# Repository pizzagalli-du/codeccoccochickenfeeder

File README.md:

# codeccoccochickenfeeder
Ultra low power chicken feeder

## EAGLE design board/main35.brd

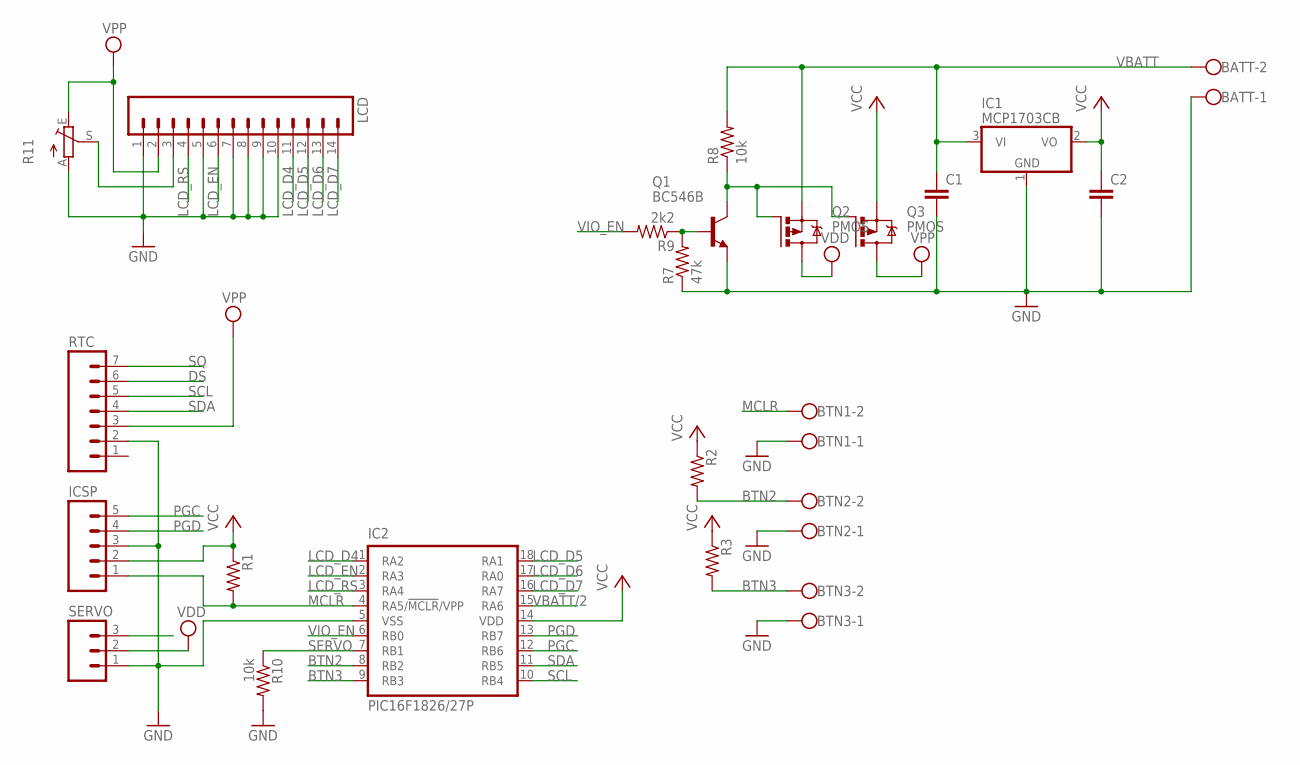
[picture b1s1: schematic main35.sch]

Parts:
BATT: W237-102
BTN1, BTN2, BTN3: W237-102
C1, C2: C-EUC0805K; C0805K
IC1: MCP1703CB; SOT23
IC2: PIC16F1826/27P; DIL18
ICSP: M05; 05P
LCD: M14; 14P
Q1: BC546B; TO92-EBC
Q2, Q3: PMOS; MICRO3
R1, R2, R3: R-US_M0805; M0805
R7: 47k; 0207/10
R8, R10: 10k; R1005
R9: 2k2; 0207/10
R11: TRIM_EU-LI10; LI10
RTC: M07; 07P
SERVO: M03; 03P

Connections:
BTN2: BTN2.2, IC2.8 (RB2), R2.2
BTN3: BTN3.2, IC2.9 (RB3), R3.2
DS: RTC.6
GND: BATT.1, BTN1.1, BTN2.1, BTN3.1, C1.2, C2.2, IC1.1 (GND), IC2.5 (VSS), ICSP.3, LCD.1, LCD.5, LCD.7, LCD.8, LCD.9, LCD.10, Q1.E, R7.1, R10.2, R11.A, RTC.2, SERVO.1
LCD_D4: IC2.1 (RA2), LCD.11
LCD_D5: IC2.18 (RA1), LCD.12
LCD_D6: IC2.17 (RA0), LCD.13
LCD_D7: IC2.16 (RA7), LCD.14
LCD_EN: IC2.2 (RA3), LCD.6
LCD_RS: IC2.3 (RA4), LCD.4
MCLR: BTN1.2, IC2.4 (RA5/!MCLR!/VPP), ICSP.1, R1.2
unnamed: LCD.3, R11.S
unnamed: Q1.B, R7.2, R9.1
PGC: IC2.12 (RB6), ICSP.5
PGD: IC2.13 (RB7), ICSP.4
SCL: IC2.10 (RB4), RTC.5
SDA: IC2.11 (RB5), RTC.4
SERVO: IC2.7 (RB1), R10.1, SERVO.3
SQ: RTC.7
VBATT: BATT.2, C1.1, IC1.3 (VI), Q2.2 (S), R8.2
VBATT/2: IC2.15 (RA6)
VCC: C2.1, IC1.2 (VO), IC2.14 (VDD), ICSP.2, Q3.2 (S), R1.1, R2.1, R3.1
VDD: Q2.3 (D), SERVO.2
VGIO: Q1.C, Q2.1 (G), Q3.1 (G), R8.1
VIO_EN: IC2.6 (RB0), R9.2
VPP: LCD.2, Q3.3 (D), R11.E, RTC.3

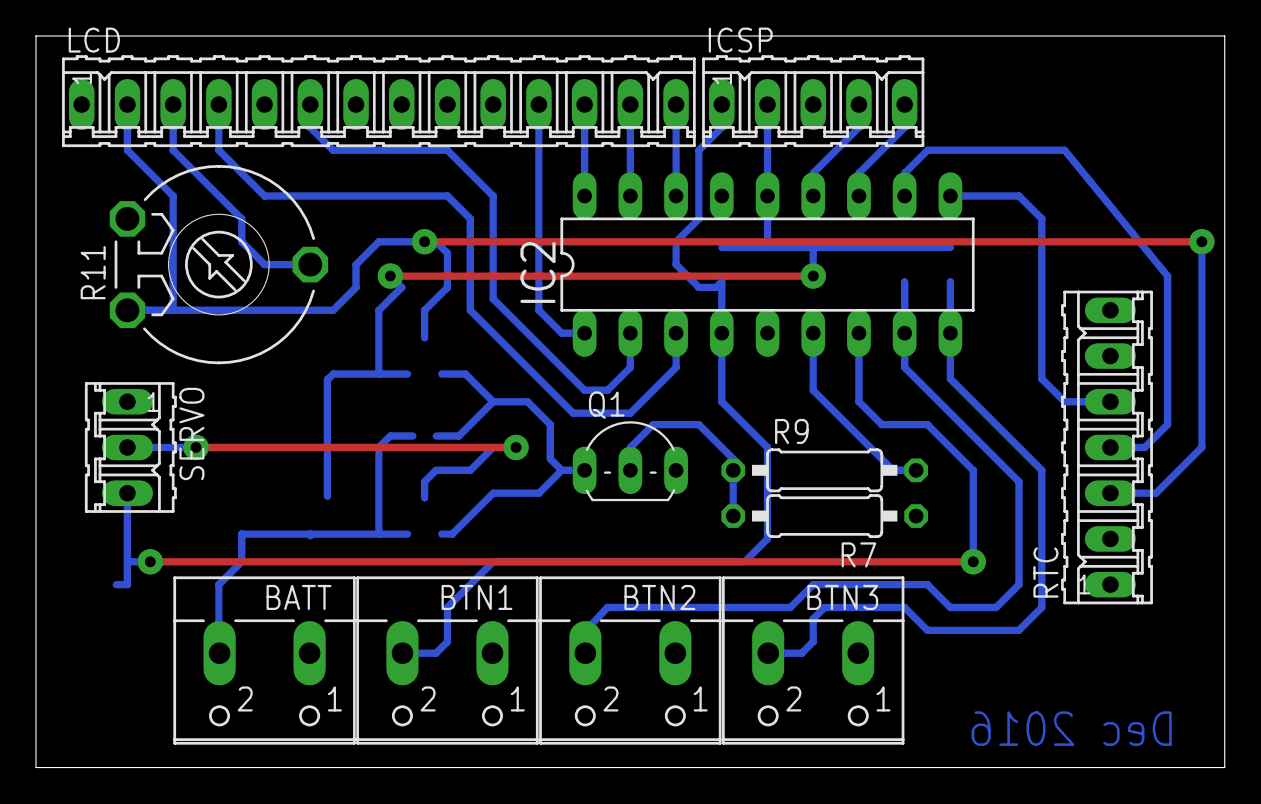
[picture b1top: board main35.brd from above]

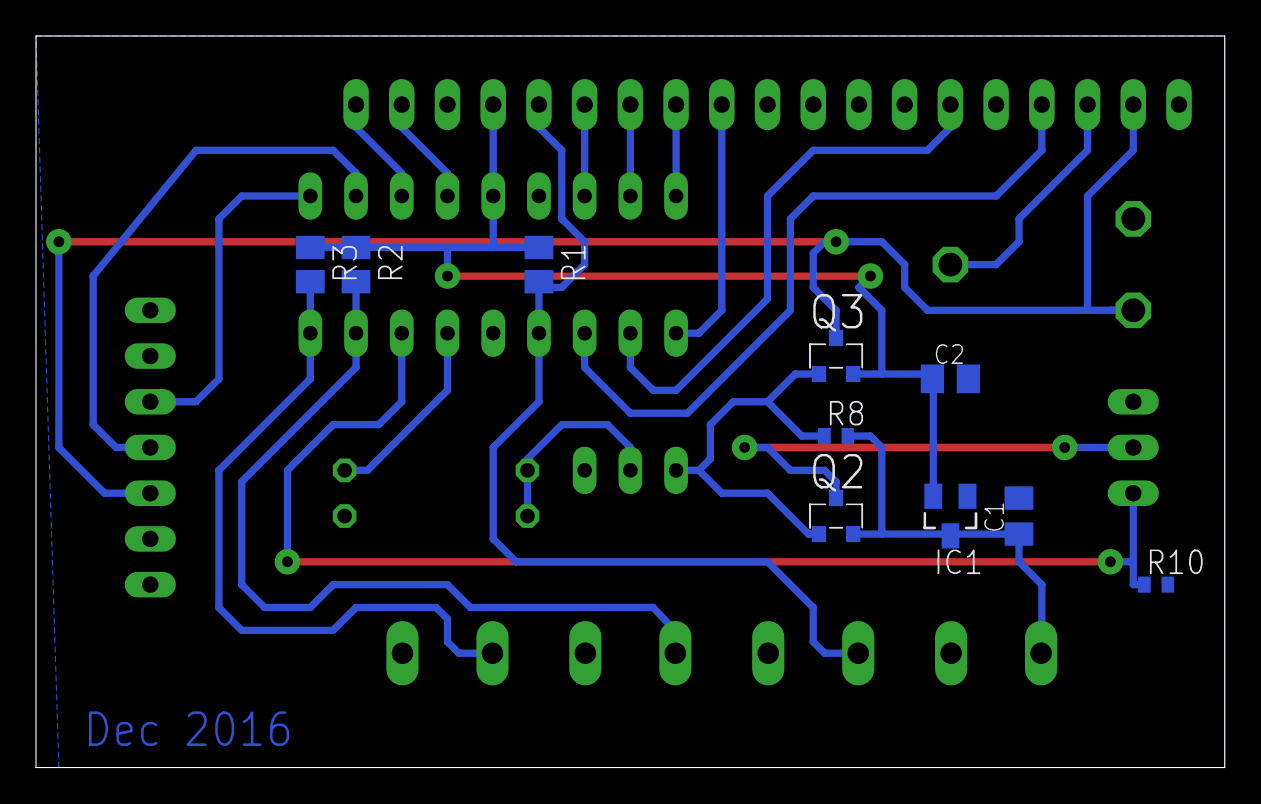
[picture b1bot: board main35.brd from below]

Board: 2 copper layers, 66.0 x 40.6 mm, 23 parts (10 on the bottom side), 23 nets.

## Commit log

2017-10-05 First release
    ADDED board
